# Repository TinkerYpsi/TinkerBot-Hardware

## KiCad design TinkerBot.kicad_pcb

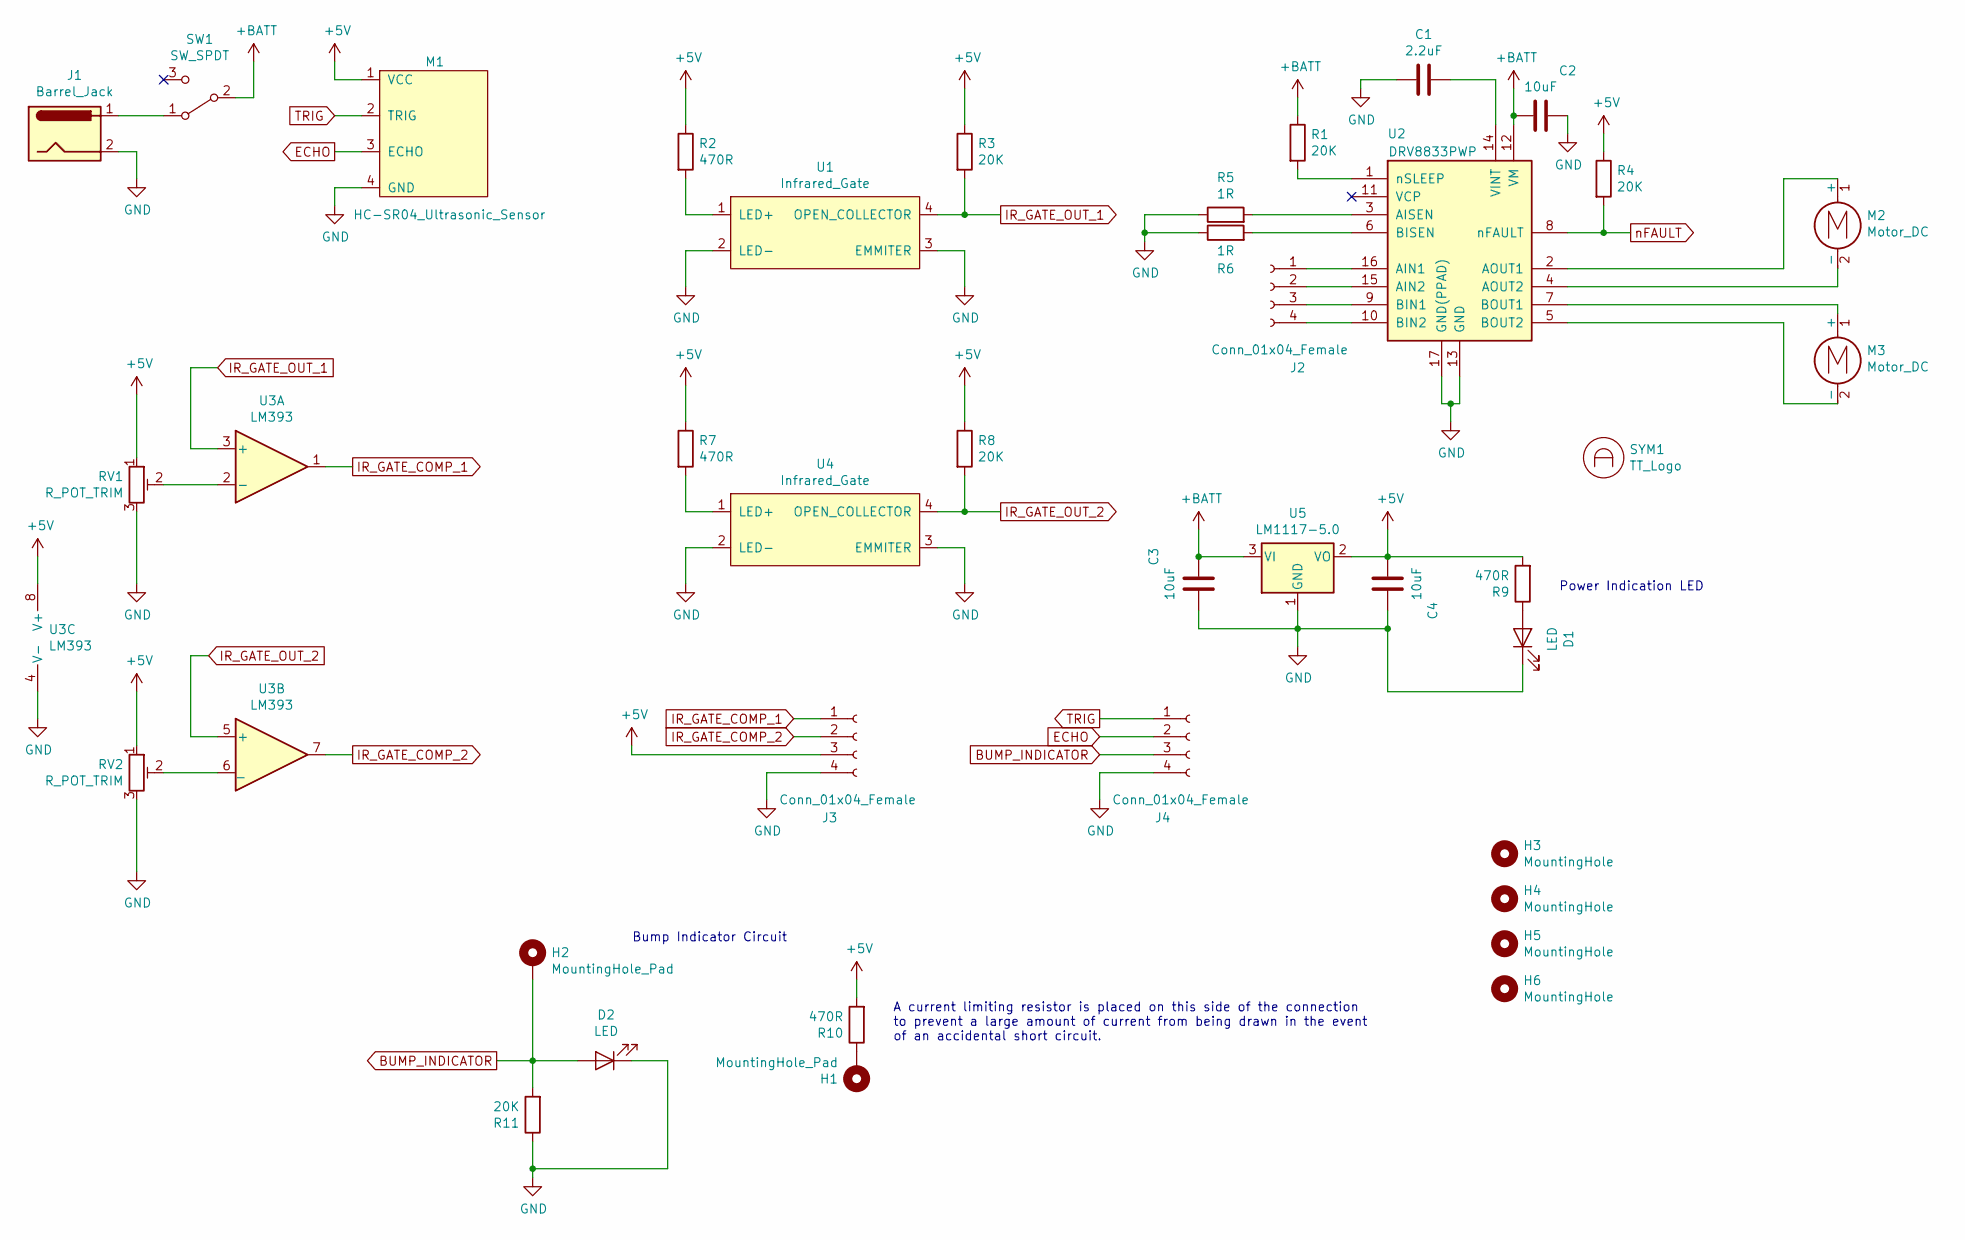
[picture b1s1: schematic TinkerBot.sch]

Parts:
C1: 2.2uF; C_Disc_D5.0mm_W2.5mm_P2.50mm
C2, C3, C4: 10uF; C_Disc_D5.0mm_W2.5mm_P5.00mm
D1, D2: LED; LED_D3.0mm
H1, H2: MountingHole_Pad; MountingHole_3mm_Pad_Via
H3, H4, H5, H6: MountingHole; MountingHole_3mm
J1: Barrel_Jack; BarrelJack_Horizontal
J2, J3, J4: Conn_01x04_Female; PinHeader_1x04_P2.54mm_Vertical
M1: HC-SR04_Ultrasonic_Sensor; HC-SR04-Labeled-Short-Silk
M2, M3: Motor_DC; PinHeader_1x02_P2.54mm_Vertical
R1, R3, R4, R8, R11: 20K; R_Axial_DIN0207_L6.3mm_D2.5mm_P10.16mm_Horizontal
R2, R7, R9, R10: 470R; R_Axial_DIN0207_L6.3mm_D2.5mm_P10.16mm_Horizontal
R5, R6: 1R; R_Axial_DIN0207_L6.3mm_D2.5mm_P10.16mm_Horizontal
RV1, RV2: R_POT_TRIM; Potentiometer_Vishay_T73YP_Vertical
SW1: SW_SPDT; SPDT_Slide_Switch_2.54mm_pitch
SYM1: TT_Logo; TinkerTech-Logo_27.6x8mm_SilkScreen
U1, U4: Infrared_Gate
U2: DRV8833PWP; HTSSOP-16-1EP_4.4x5mm_P0.65mm_EP3.4x5mm_Mask2.46x2.31mm_The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
U3: LM393; DIP-8_W7.62mm_Socket
U5: LM1117-5.0; TO-220-3_Horizontal_TabDown

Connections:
+5V: C4.2, J3.3, M1.1 (VCC), R2.1, R3.1, R4.1, R7.1, R8.1, R9.2, R10.2, RV1.1, RV2.1, U3.8 (V+), U5.2 (VO)
+BATT: C2.2, C3.1, R1.1, SW1.2 (B), U2.12 (VM), U5.3 (VI)
BUMP_INDICATOR: D2.2 (A), H2.1, J4.3, R11.2
ECHO: J4.2, M1.3 (ECHO)
GND: C1.2, C2.1, C3.2, C4.1, D1.1 (K), D2.1 (K), J1.2, J3.4, J4.4, M1.4 (GND), R5.1, R6.1, R11.1, RV1.3, RV2.3, U1.2 (LED-), U1.3 (EMMITER), U2.13 (GND), U2.17 (GND(PPAD)), U3.4 (V-), U4.2 (LED-), U4.3 (EMMITER), U5.1 (GND)
IR_GATE_COMP_1: J3.1, U3.1
IR_GATE_COMP_2: J3.2, U3.7
IR_GATE_OUT_1: R3.2, U1.4 (OPEN_COLLECTOR), U3.3 (+)
IR_GATE_OUT_2: R8.2, U3.5 (+), U4.4 (OPEN_COLLECTOR)
unnamed: C1.1, U2.14 (VINT)
unnamed: D1.2 (A), R9.1
unnamed: H1.1, R10.1
unnamed: J1.1, SW1.1 (A)
unnamed: J2.1, U2.16 (AIN1)
unnamed: J2.2, U2.15 (AIN2)
unnamed: J2.3, U2.9 (BIN1)
unnamed: J2.4, U2.10 (BIN2)
unnamed: M2.1 (+), U2.2 (AOUT1)
unnamed: M2.2 (-), U2.4 (AOUT2)
unnamed: M3.1 (+), U2.7 (BOUT1)
unnamed: M3.2 (-), U2.5 (BOUT2)
unnamed: R1.2, U2.1 (nSLEEP)
unnamed: R2.2, U1.1 (LED+)
unnamed: R5.2, U2.3 (AISEN)
unnamed: R6.2, U2.6 (BISEN)
unnamed: R7.2, U4.1 (LED+)
unnamed: RV1.2, U3.2 (-)
unnamed: RV2.2, U3.6 (_)
TRIG: J4.1, M1.2 (TRIG)
nFAULT: R4.2, U2.8 (nFAULT)

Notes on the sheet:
Power Indication LED
Bump Indicator Circuit
A current limiting resistor is placed on this side of the connection to prevent a large amount of current from being drawn in the event of an accidental short circuit.

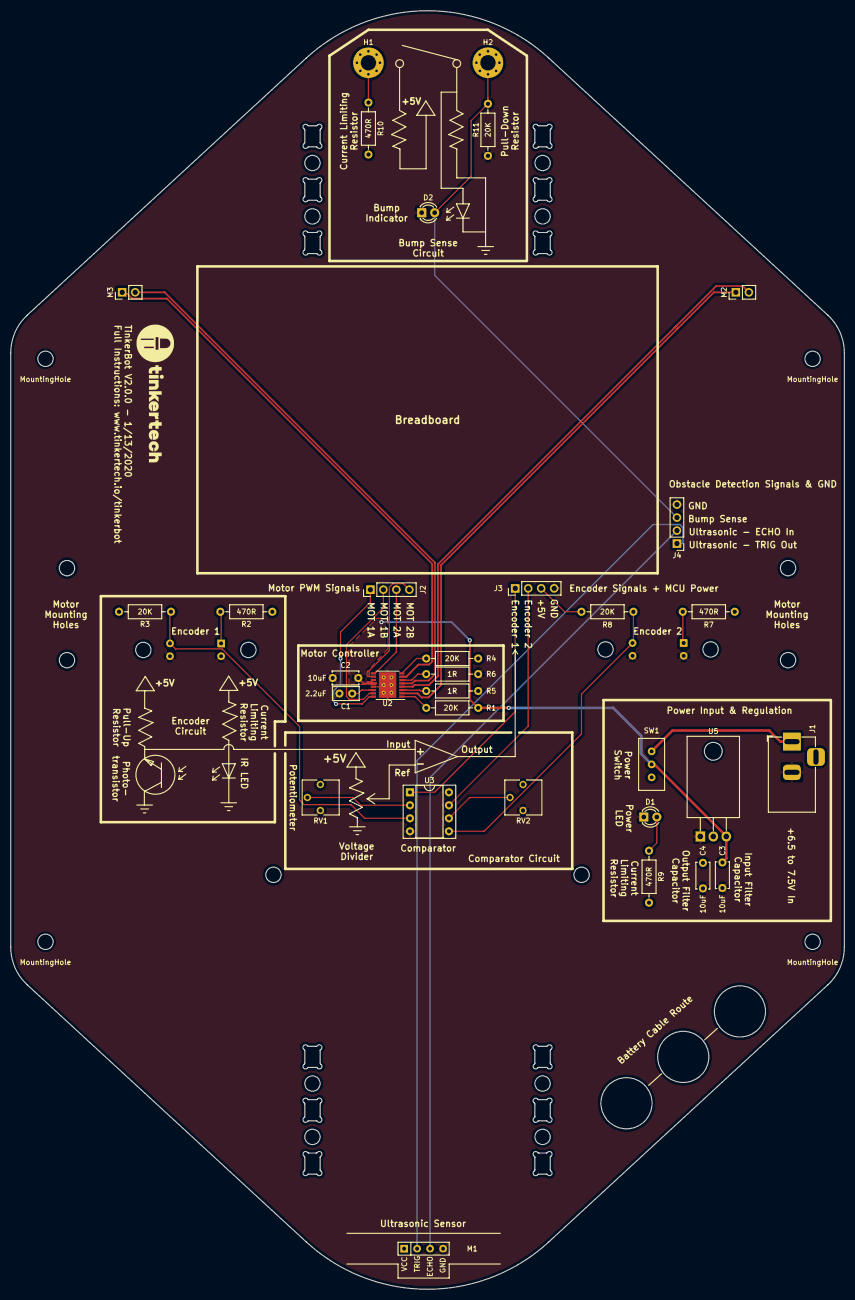
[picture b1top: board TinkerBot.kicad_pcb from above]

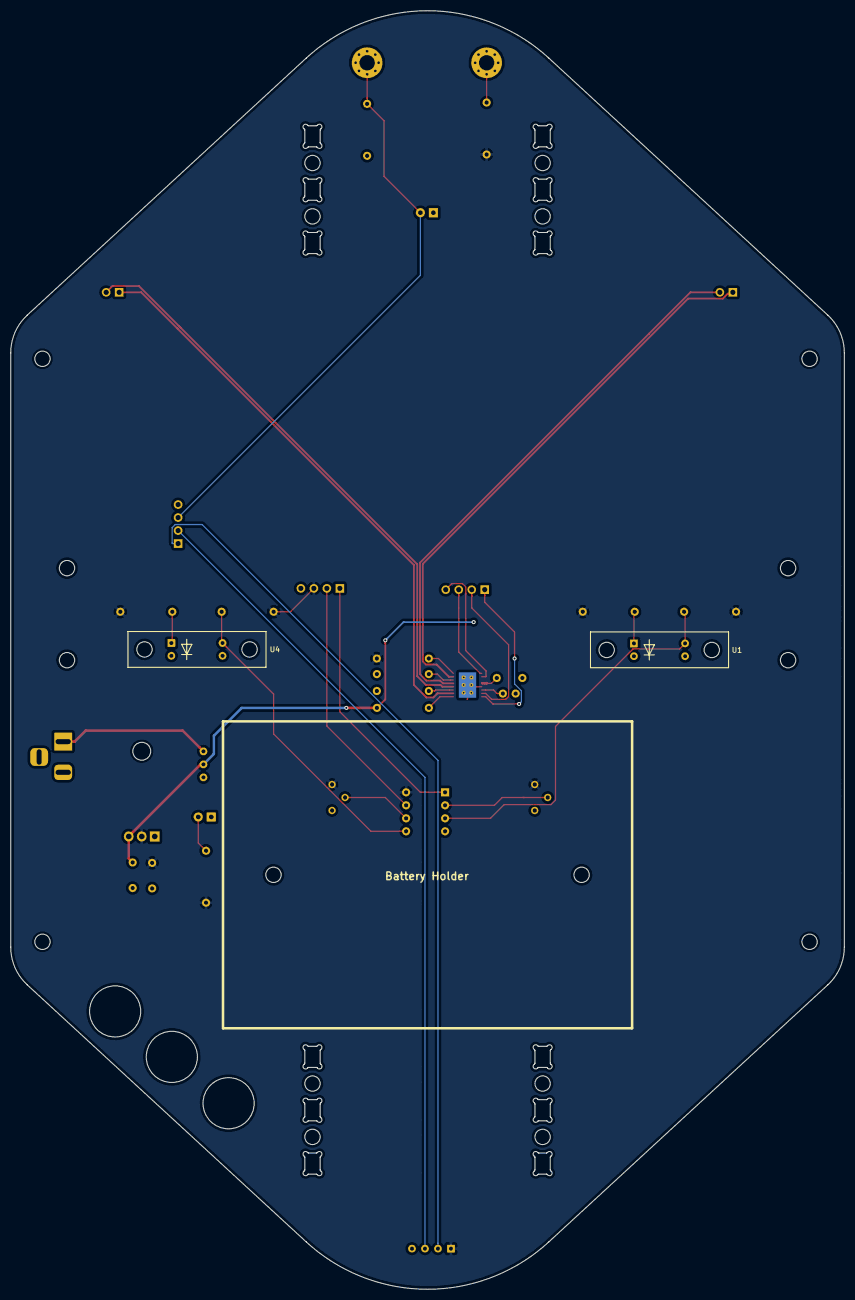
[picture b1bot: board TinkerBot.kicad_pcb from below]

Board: 2 copper layers, 163.0 x 250.0 mm, 39 parts (2 on the bottom side), 30 nets.

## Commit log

2020-02-26 :tada: Added .gitattributes & .gitignore files
2020-02-26 Initial Commit - V2.0.1
